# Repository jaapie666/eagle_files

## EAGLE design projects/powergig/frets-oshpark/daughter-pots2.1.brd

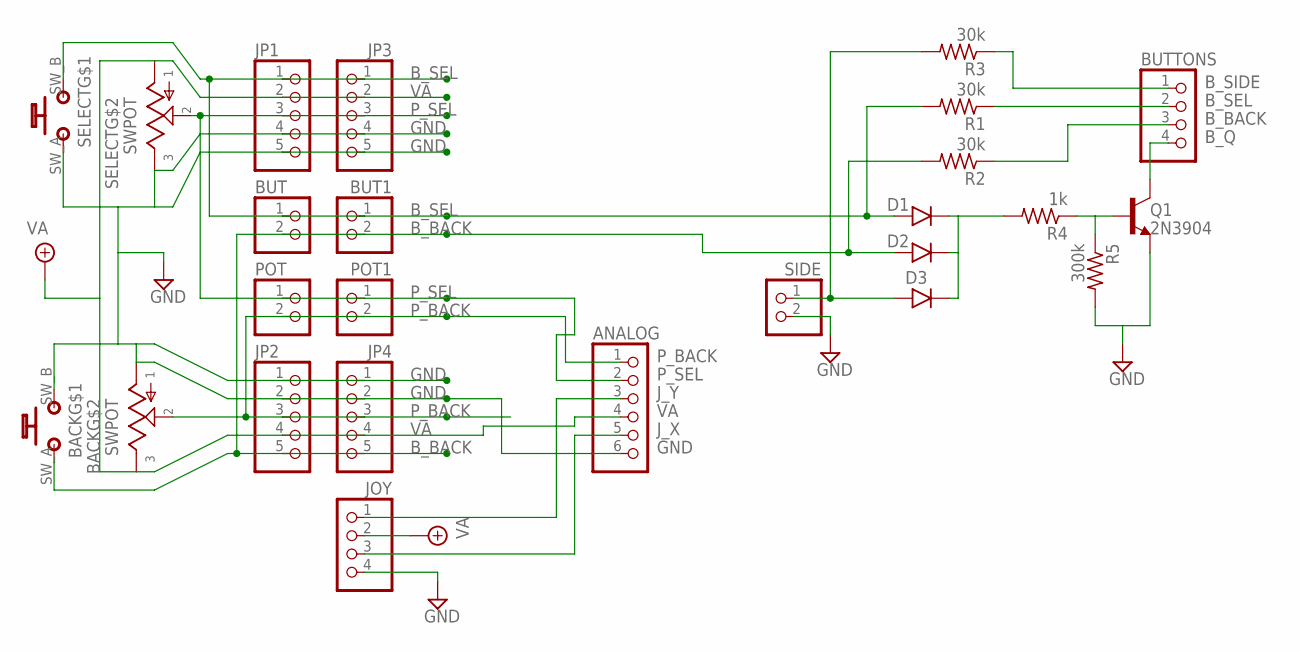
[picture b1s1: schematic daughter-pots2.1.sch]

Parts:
ANALOG: PINHD-1X6; 1X06
BACK: SWPOT
BUT, BUT1: PINHD-1X2; 1X02
BUTTONS: PINHD-1X4; 1X04
D1: 1N4148-3; DO35-3
D2: 1N4148-2; DO35-2
D3: 1N4148-4; DO35-4
JOY: PINHD-1X4; 1X04
JP1, JP2, JP3, JP4: PINHD-1X5; 1X05
POT, POT1: PINHD-1X2; 1X02
Q1: 2N3904; TO92-
R1, R2, R3: 30k; R0207/3
R4: 1k; R0207/3
R5: 300k; R0207/1V
SELECT: SWPOT
SIDE: PINHD-1X2; 1X02

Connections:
B_BACK: BACK.SW_A (B_A), BUT.2, BUT1.2, D2.A, JP2.5, JP4.5, R2.2
B_Q: BUTTONS.4, Q1.1 (C)
B_SEL: BUT.1, BUT1.1, D1.A, JP1.1, JP3.1, R1.2, SELECT.SW_B (B_B)
B_SIDE: D3.A, R3.2, SIDE.1
GND: ANALOG.6, BACK.POT_B, BACK.SW_B (B_B), JOY.4, JP1.4, JP1.5, JP2.1, JP2.2, JP3.4, JP3.5, JP4.1, JP4.2, Q1.3 (E), R5.2, SELECT.POT_A, SELECT.SW_A (B_A), SIDE.2
J_X: ANALOG.5, JOY.3
J_Y: ANALOG.3, JOY.1
unnamed: Q1.2 (B), R4.1, R5.1
unnamed: BUTTONS.2, R1.1
unnamed: BUTTONS.3, R2.1
unnamed: D1.C, D2.C, D3.C, R4.2
unnamed: BUTTONS.1, R3.1
P_BACK: ANALOG.1, BACK.POT_W, JP2.3, JP4.3, POT.2, POT1.2
P_SEL: ANALOG.2, JP1.3, JP3.3, POT.1, POT1.1, SELECT.POT_W
VA: ANALOG.4, BACK.POT_A, JOY.2, JP1.2, JP2.4, JP3.2, JP4.4, SELECT.POT_B

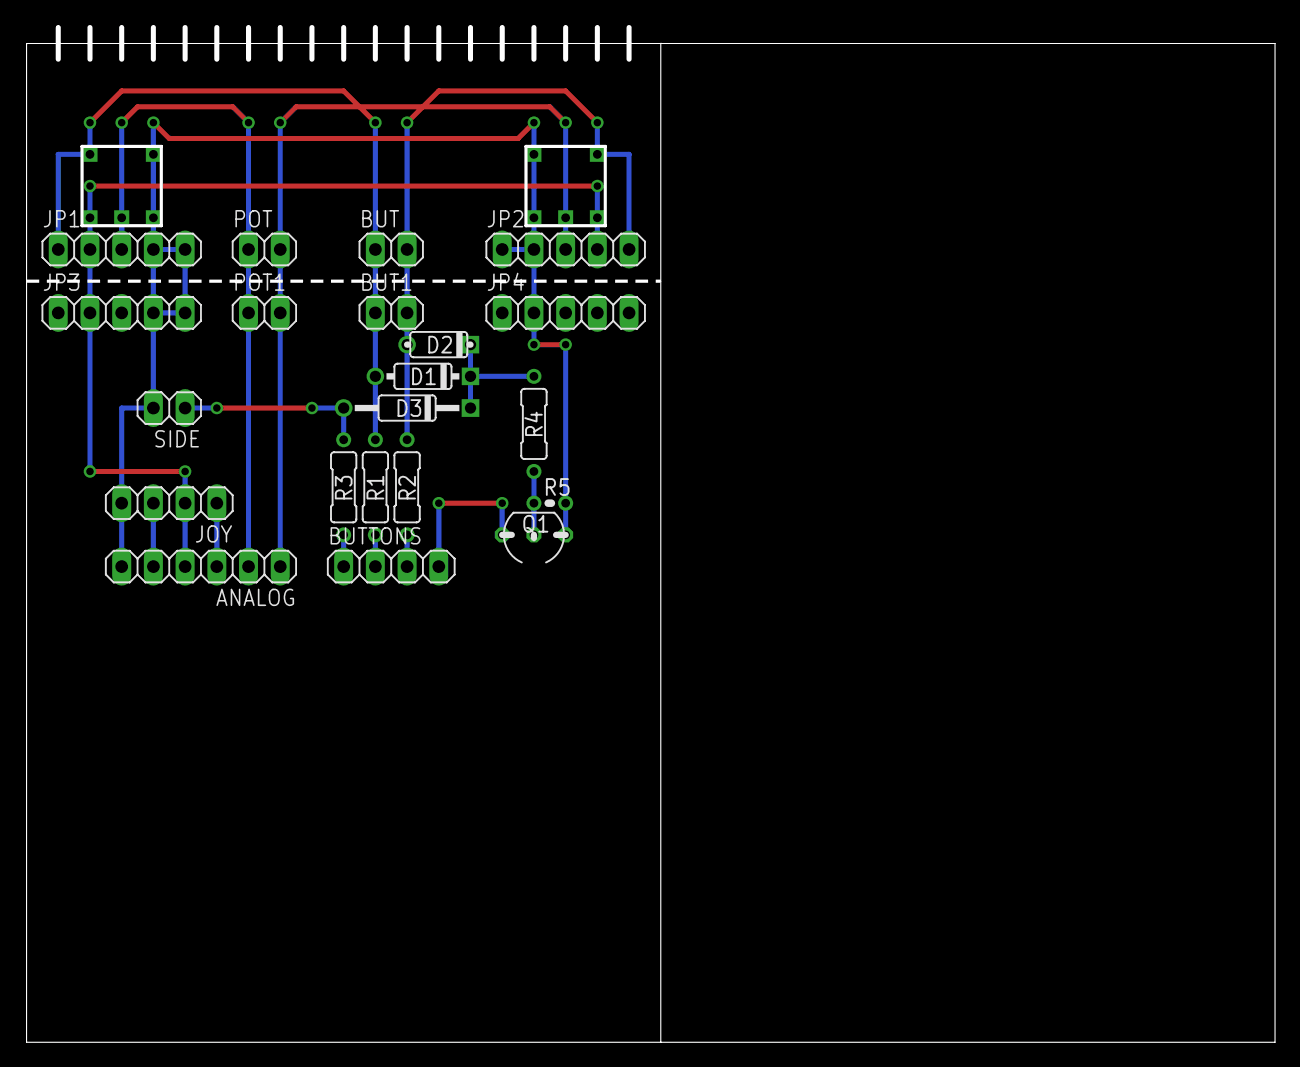
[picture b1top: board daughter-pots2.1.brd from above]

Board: 2 copper layers, 100.0 x 81.3 mm, 23 parts (0 on the bottom side), 15 nets.

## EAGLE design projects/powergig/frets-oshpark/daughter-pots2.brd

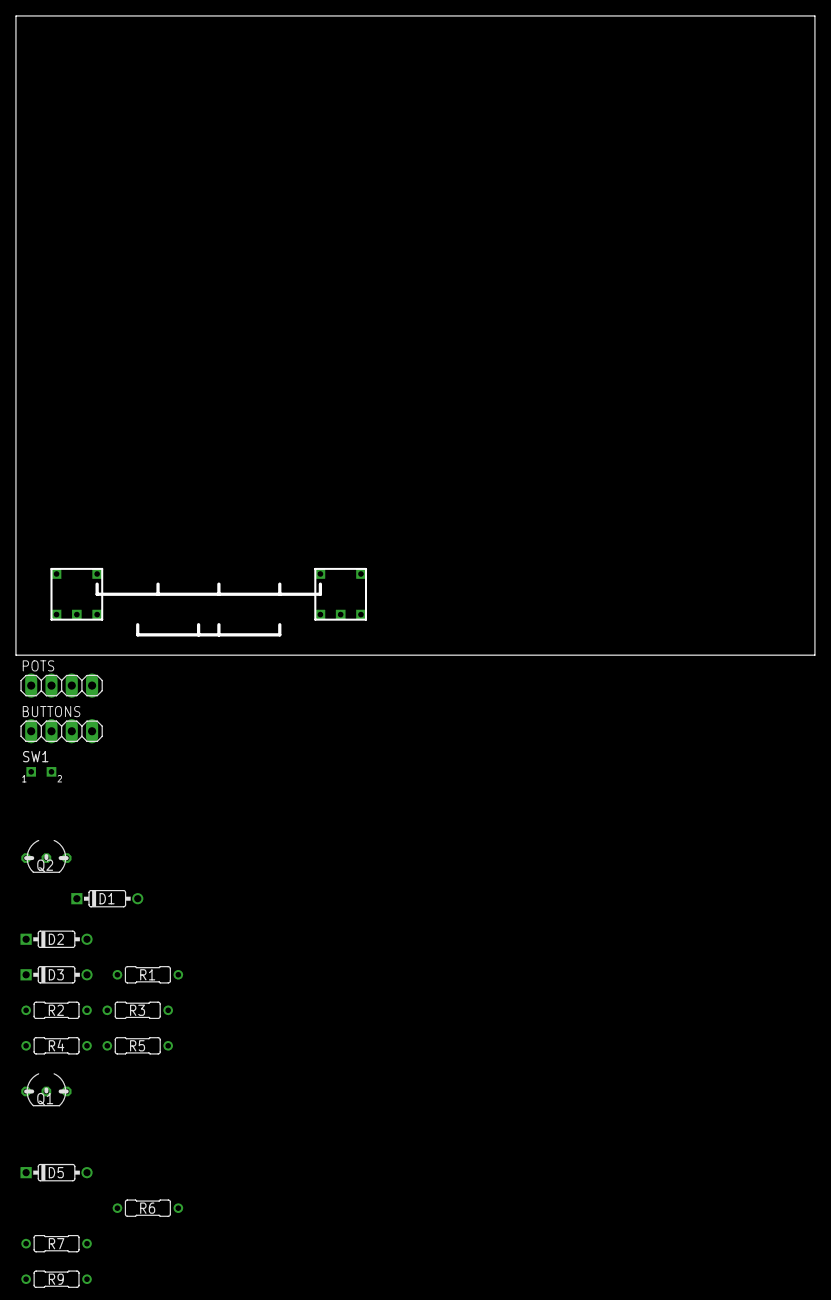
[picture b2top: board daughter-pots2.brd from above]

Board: 2 copper layers, 100.0 x 80.0 mm, 19 parts (0 on the bottom side), 15 nets, no tracks yet.

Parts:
BACK: SWPOT
BUTTONS: 1X04
D1, D2, D3, D5: 1N4148-3; DO35-3
POTS: 1X04
Q1, Q2: 2N3904; TO92-
R1, R6: 1K; R0207/3
R2, R7: 300K; R0207/3
R3, R4, R5, R9: 30k; R0207/3
SELECT: SWPOT
SW1: MOMENTARYSPST1; SPST

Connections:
BPOT: BACK.POT_W, POTS.2
B_BACK: BUTTONS.1, R3.1
B_SEL: BUTTONS.2, R4.1
B_SIDE: BUTTONS.3, R5.1
GND: BACK.POT_A, BACK.SW_B, POTS.4, Q1.3, Q2.3, R2.1, R7.1, SELECT.POT_A, SELECT.SW_B, SW1.2
unnamed: Q2.2, R1.2, R2.2
unnamed: D1.C, D2.C, D3.C, R1.1
unnamed: Q1.2, R6.2, R7.2
unnamed: D2.A, R4.2
unnamed: BACK.SW_A, D1.A, R3.2
unnamed: D3.A, R5.2, SW1.1
unnamed: D5.A, R9.2
Q: BUTTONS.4, Q2.1
SPOT: POTS.3, SELECT.POT_W
VA: BACK.POT_B, POTS.1, SELECT.POT_B

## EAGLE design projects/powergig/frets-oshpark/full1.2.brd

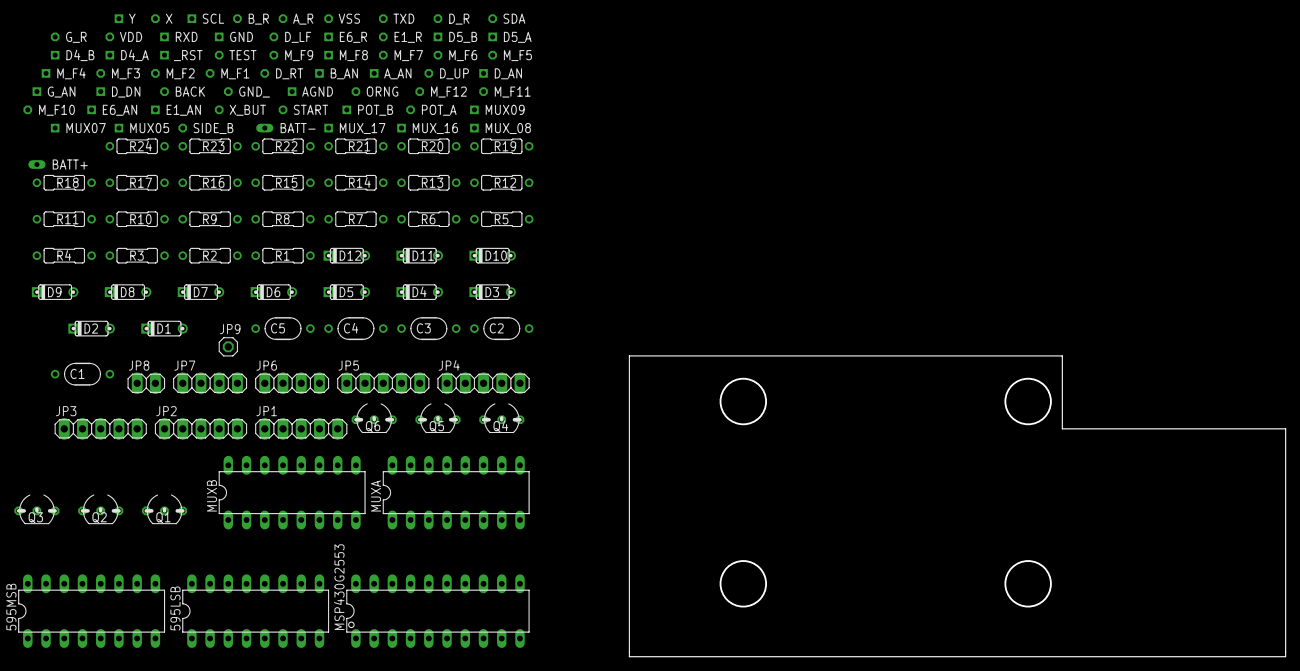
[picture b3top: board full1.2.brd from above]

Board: 2 copper layers, 91.4 x 41.9 mm, 121 parts (0 on the bottom side), 83 nets, no tracks yet.

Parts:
595LSB, 595MSB: 74LS595N; DIL16
AGND: SQUARE
A_AN: SQUARE
A_R: OCTOGON
BACK: OCTOGON
BATT+: LONG
BATT-: LONG
B_AN: SQUARE
B_R: OCTOGON
C1, C2, C3, C4, C5: 100n; 050X030_050_3
D1, D2, D3, D4, D5, D6, D7, D8, D9, D10, D11, D12: 1N4148-2; DO35-2
D4_A, D4_B, D5_A, D5_B: SQUARE
D_AN: SQUARE
D_DN: SQUARE
D_LF: OCTOGON
D_R: OCTOGON
D_RT: OCTOGON
D_UP: OCTOGON
E1_AN, E6_AN, E6_R: SQUARE
E1_R: OCTOGON
GND: SQUARE
GND_: OCTOGON
G_AN: SQUARE
G_R: OCTOGON
JP1, JP2, JP3, JP4, JP5: 1X05
JP6, JP7: 1X04
JP8: 1X02
JP9: 1X01
MSP430G2553: G2XX3---N20; N20
MUX05, MUX07, MUX09: SQUARE
MUXA: 4051N; DIL16
MUXB: 4051N; DIL16
MUX_08, MUX_16, MUX_17: SQUARE
M_F1, M_F2, M_F3, M_F5, M_F6, M_F7, M_F9, M_F10, M_F11, M_F12: OCTOGON
M_F4, M_F8: SQUARE
ORNG: OCTOGON
POT_A: OCTOGON
POT_B: SQUARE
Q1, Q2, Q3, Q4, Q5, Q6: 2N3904; TO92-
R1, R3, R5, R7, R9, R11: 300k; R0207/3
R2, R4, R6, R8, R10, R12: 1k; R0207/3
R13, R14, R15, R16, R17, R18, R19, R20, R21, R22, R23, R24: 30k; R0207/3
RXD: SQUARE
SCL: SQUARE
SDA: OCTOGON
SIDE_B: OCTOGON
START: OCTOGON
TEST: OCTOGON
TXD: OCTOGON
VDD: OCTOGON
VSS: OCTOGON
X: OCTOGON
X_BUT: OCTOGON
Y: SQUARE
_RST: SQUARE

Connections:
A_AN: A_AN.1, MUXB.2
A_IN: MSP430G2553.2, MUXA.3, MUXB.3
BACK: BACK.1, R18.1
B_AN: B_AN.1, MUXB.12
D0: E6_R.1, MSP430G2553.5, Q3.1
D1: A_R.1, MSP430G2553.6, Q2.1
D2: D_R.1, MSP430G2553.7, Q1.1
D3: G_R.1, MSP430G2553.8, Q6.1
D4: B_R.1, MSP430G2553.9, Q5.1
D5: E1_R.1, MSP430G2553.10, Q4.1
D_AN: D_AN.1, MUXB.5
D_DOWN: D_DN.1, R22.1
D_RIGHT: D_RT.1, R21.1
D_UP: D_UP.1, R19.1
E1_AN: E1_AN.1, MUXB.15
E6_AN: E6_AN.1, MUXB.4
GND: 595LSB.8, 595LSB.13, 595MSB.8, 595MSB.13, BATT-.1, C1.2, C2.2, C3.2, C4.2, C5.2, GND.1, GND_.1, MSP430G2553.20, MUXA.7, MUXA.8, MUXB.7, MUXB.8, Q1.3, Q2.3, Q3.3, Q4.3, Q5.3, Q6.3, R1.2, R3.2, R5.2, R7.2, R9.2, R11.2, VSS.1
G_AN: G_AN.1, MUXB.1
INH_A: MSP430G2553.18, MUXA.6
INH_B: MSP430G2553.19, MUXB.6
JOY_X: MUXA.4, X.1
JOY_Y: MUXA.2, Y.1
MUX05: MUX05.1, MUXA.12
MUX07: MUX07.1, MUXA.15
MUX08: MUXA.14, MUX_08.1
MUX09: MUX09.1, MUXA.13
MUX16: MUXB.14, MUX_16.1
MUX17: MUXB.13, MUX_17.1
unnamed: 595LSB.14, 595MSB.9
unnamed: Q2.2, R3.1, R4.2
unnamed: D3.A, R15.2
unnamed: D5.C, D9.C, R4.1
unnamed: Q3.2, R5.1, R6.2
unnamed: Q1.2, R1.1, R2.2
unnamed: D6.C, D8.C, R2.1
unnamed: D4.A, R16.2
unnamed: D5.A, R17.2
unnamed: D4.C, D7.C, R6.1
unnamed: Q4.2, R7.1, R8.2
unnamed: D6.A, R18.2
unnamed: D3.C, D12.C, R8.1
unnamed: Q5.2, R9.1, R10.2
unnamed: D1.A, R13.2
unnamed: D2.C, D11.C, R10.1
unnamed: Q6.2, R11.1, R12.2
unnamed: D2.A, R14.2
unnamed: D1.C, D10.C, R12.1
unnamed: D7.A, R19.2
unnamed: D8.A, R20.2
unnamed: D9.A, R21.2
unnamed: D10.A, R22.2
unnamed: D4_B.1, R14.1
unnamed: D5_B.1, R15.1
unnamed: D11.A, R23.2
unnamed: D12.A, R24.2
unnamed: D4_A.1, R23.1
unnamed: D5_A.1, R24.1
POT_B: MUXA.1, POT_B.1
RCK: 595LSB.12, 595MSB.12, MSP430G2553.13
RXD: MSP430G2553.3, RXD.1
SCK: 595LSB.11, 595MSB.11, MSP430G2553.12
SCL: MSP430G2553.14, SCL.1
SDA: MSP430G2553.15, SDA.1
SER: 595MSB.14, MSP430G2553.11
SR0: 595LSB.7, MUXA.11, MUXB.11
SR1: 595LSB.6, MUXA.10, MUXB.10
SR2: 595LSB.5, MUXA.9, MUXB.9
SR4: 595LSB.3, M_F12.1
SR5: 595LSB.2, M_F11.1
SR6: 595LSB.1, M_F10.1
SR7: 595LSB.15, M_F9.1
SR8: 595MSB.7, M_F8.1
SR10: 595MSB.5, M_F6.1
SR11: 595MSB.4, M_F5.1
SR12: 595MSB.3, M_F4.1
SR14: 595MSB.1, M_F2.1
SR15: 595MSB.15, M_F1.1
START: R13.1, START.1
TEST: MSP430G2553.17, TEST.1
TXD: MSP430G2553.4, TXD.1
VA: 595LSB.10, 595LSB.16, 595MSB.10, 595MSB.16, BATT+.1, C1.1, C2.1, C3.1, C4.1, C5.1, MSP430G2553.1, MUXA.16, MUXB.16, VDD.1
X_BUTTON: R16.1, X_BUT.1
_RST: MSP430G2553.16, _RST.1

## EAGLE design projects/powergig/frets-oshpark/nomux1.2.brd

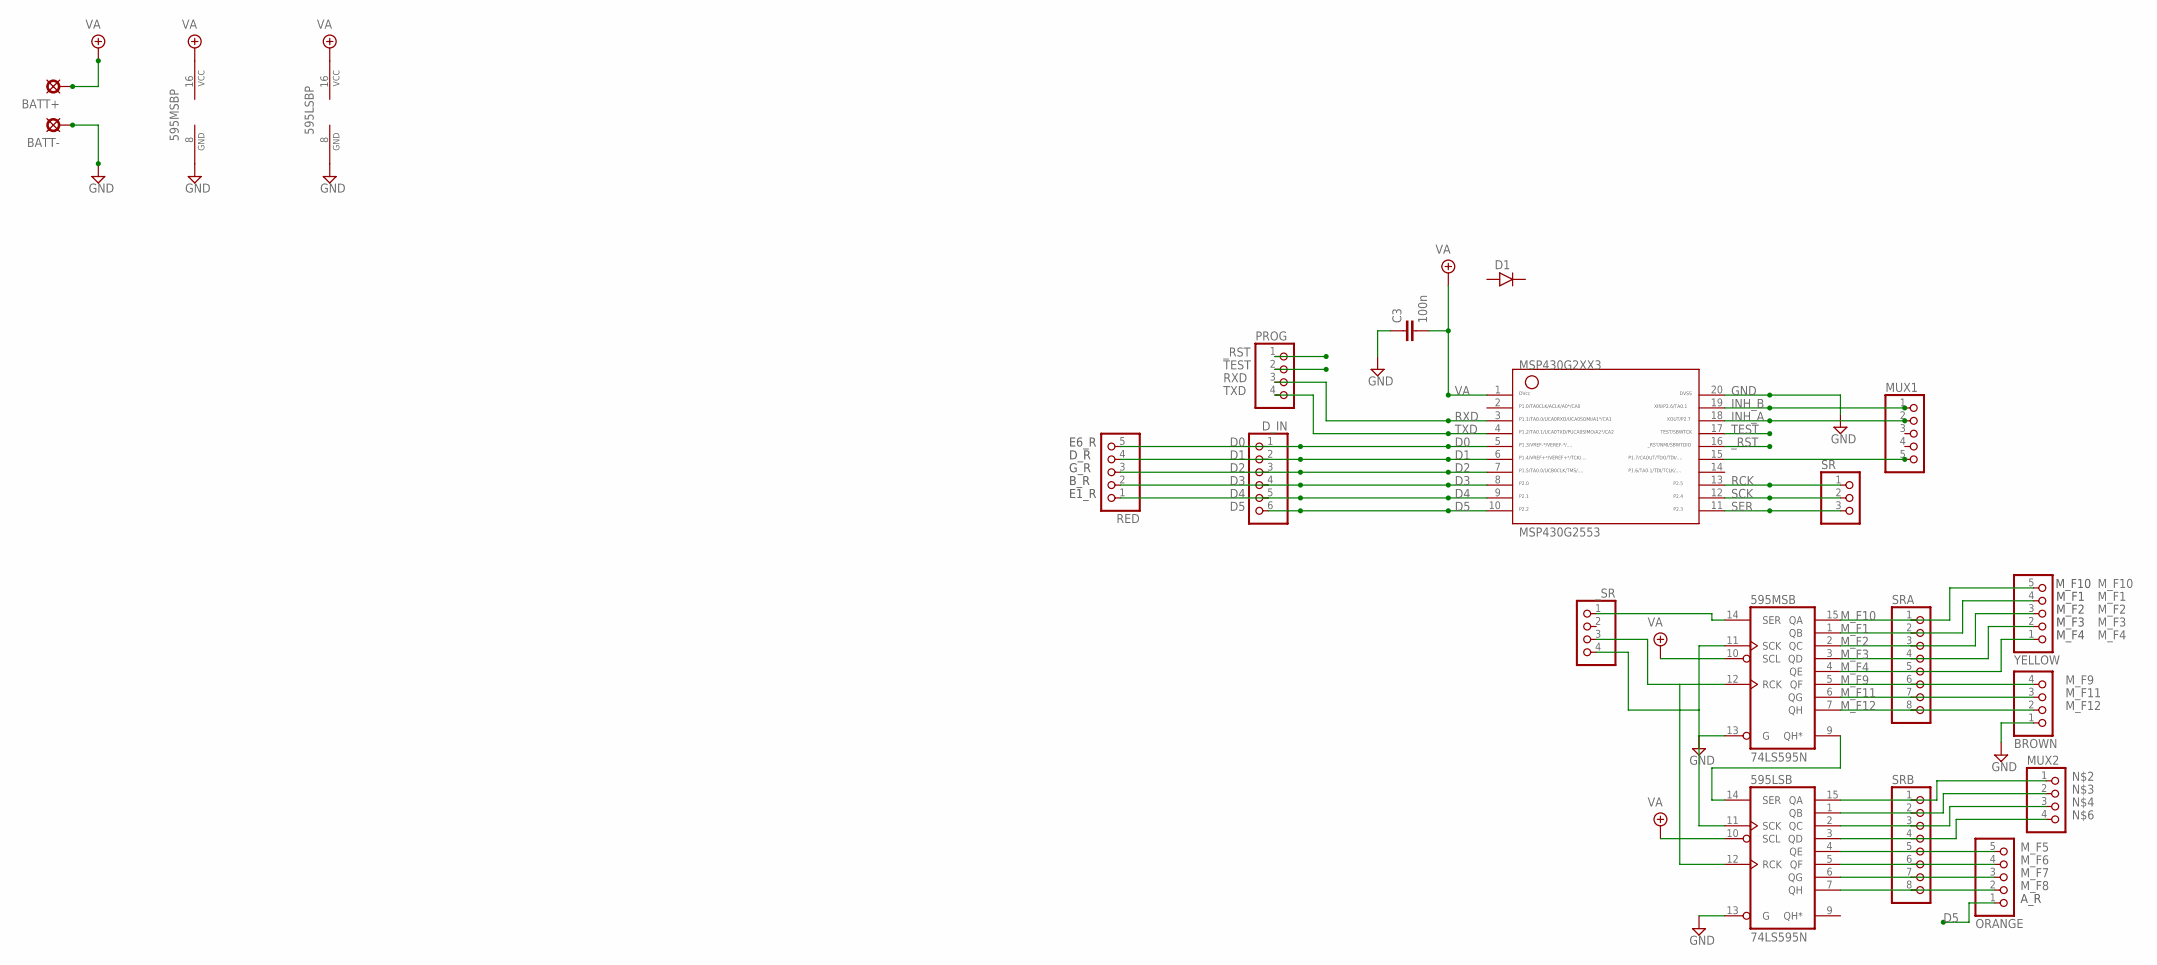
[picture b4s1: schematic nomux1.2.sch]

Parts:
595LSB, 595MSB: 74LS595N; DIL16
BATT+: PADL; LONG
BATT-: PADL; LONG
BROWN: PINHD-1X4; 1X04
C3: 100n; 050X030_050_3
D1: 1N400X.4; DO41-4
D_IN: PINHD-1X6; 1X06
MSP430G2553: G2XX3---N20; N20
MUX1: PINHD-1X5; 1X05
MUX2: PINHD-1X4; 1X04
ORANGE: PINHD-1X5; 1X05
PROG: PINHD-1X4; 1X04
RED: PINHD-1X5; 1X05
SR: PINHD-1X3; 1X03
SRA: PINHD-1X8; 1X08
SRB: PINHD-1X8; 1X08
YELLOW: PINHD-1X5; 1X05
_SR: PINHD-1X4; 1X04

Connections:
D0: D_IN.1, MSP430G2553.5, RED.5
D1: D_IN.2, MSP430G2553.6, RED.4
D2: D_IN.3, MSP430G2553.7, RED.3
D3: D_IN.4, MSP430G2553.8, RED.2
D4: D_IN.5, MSP430G2553.9, RED.1
D5: D_IN.6, MSP430G2553.10, ORANGE.1
GND: 595LSB.8 (GND), 595LSB.13 (G), 595MSB.8 (GND), 595MSB.13 (G), BATT-.1, BROWN.1, C3.1, MSP430G2553.20
INH_A: MSP430G2553.18, MUX1.2
INH_B: MSP430G2553.19, MUX1.1
M_F1: 595MSB.1 (QB), SRA.2, YELLOW.4
M_F2: 595MSB.2 (QC), SRA.3, YELLOW.3
M_F3: 595MSB.3 (QD), SRA.4, YELLOW.2
M_F4: 595MSB.4 (QE), SRA.5, YELLOW.1
M_F5: 595LSB.4 (QE), ORANGE.5, SRB.5
M_F6: 595LSB.5 (QF), ORANGE.4, SRB.6
M_F7: 595LSB.6 (QG), ORANGE.3, SRB.7
M_F8: 595LSB.7 (QH), ORANGE.2, SRB.8
M_F9: 595MSB.5 (QF), BROWN.4, SRA.6
M_F10: 595MSB.15 (QA), SRA.1, YELLOW.5
M_F11: 595MSB.6 (QG), BROWN.3, SRA.7
M_F12: 595MSB.7 (QH), BROWN.2, SRA.8
unnamed: 595LSB.14 (SER), 595MSB.9 (QH*)
unnamed: 595LSB.15 (QA), MUX2.1, SRB.1
unnamed: 595LSB.1 (QB), MUX2.2, SRB.2
unnamed: 595LSB.2 (QC), MUX2.3, SRB.3
unnamed: 595LSB.3 (QD), MUX2.4, SRB.4
unnamed: MSP430G2553.15, MUX1.5
unnamed: 595MSB.14 (SER), _SR.1
unnamed: 595LSB.11 (SCK), 595MSB.11 (SCK), _SR.4
unnamed: 595LSB.12 (RCK), 595MSB.12 (RCK), _SR.3
RCK: MSP430G2553.13, SR.1
RXD: MSP430G2553.3, PROG.3
SCK: MSP430G2553.12, SR.2
SER: MSP430G2553.11, SR.3
TEST: MSP430G2553.17, PROG.2
TXD: MSP430G2553.4, PROG.4
VA: 595LSB.10 (SCL), 595LSB.16 (VCC), 595MSB.10 (SCL), 595MSB.16 (VCC), BATT+.1, C3.2, MSP430G2553.1
_RST: MSP430G2553.16, PROG.1

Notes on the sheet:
M_F10
M_F1
M_F2
M_F3
M_F4
E6_R
D_R
G_R
B_R
E1_R
A_R

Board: 2 copper layers, 19 parts (0 on the bottom side), 38 nets, no tracks yet.

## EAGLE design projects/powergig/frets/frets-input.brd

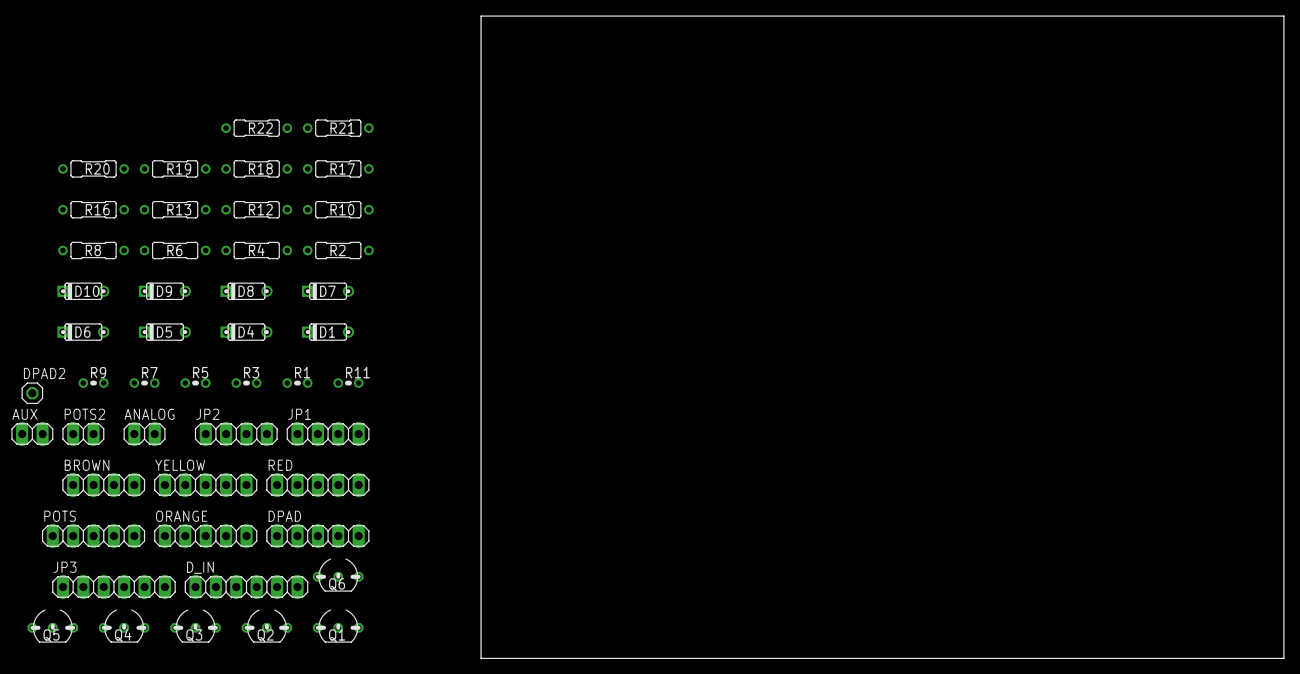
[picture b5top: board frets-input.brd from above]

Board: 2 copper layers, 100.0 x 80.0 mm, 48 parts (0 on the bottom side), 49 nets, no tracks yet.

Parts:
ANALOG: 1X02
AUX: 1X02
BROWN: 1X04
D1, D4, D5, D6, D7, D8, D9, D10: 1N4148-2; DO35-2
DPAD: 1X05
DPAD2: 1X01
D_IN: 1X06
JP1, JP2: 1X04
JP3: 1X06
ORANGE: 1X05
POTS: 1X05
POTS2: 1X02
Q1, Q2, Q3, Q4, Q5, Q6: 2N3904; TO92-
R1, R3, R5, R7, R9, R11: 300k; R0207/1V
R2, R4, R6, R8, R10, R12: 1k; R0207/3
R13, R16, R17, R18, R19, R20, R21, R22: 30k; R0207/3
RED: 1X05
YELLOW: 1X05

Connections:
D0: D_IN.1, Q3.1, RED.5
D1: D_IN.2, ORANGE.5, Q2.1
D2: D_IN.3, Q1.1, RED.4
D3: D_IN.4, Q6.1, RED.3
D4: D_IN.5, Q5.1, RED.2
D5: D_IN.6, Q4.1, RED.1
D_DOWN: DPAD.1, R22.1
D_LEFT: DPAD.2, R20.1
D_RIGHT: DPAD.3, R21.1
D_UP: DPAD.4, R19.1
GND: BROWN.1, DPAD2.1, JP3.6, POTS2.1, Q1.3, Q2.3, Q3.3, Q4.3, Q5.3, Q6.3, R1.2, R3.2, R5.2, R7.2, R9.2, R11.2
M_F1: JP1.1, YELLOW.4
M_F2: JP1.2, YELLOW.3
M_F3: JP1.3, YELLOW.2
M_F4: JP1.4, YELLOW.1
M_F5: JP2.1, ORANGE.4
M_F6: JP2.2, ORANGE.3
M_F7: JP2.3, ORANGE.2
M_F8: JP2.4, ORANGE.1
M_F9: BROWN.4, JP3.1
M_F10: JP3.2, YELLOW.5
M_F11: BROWN.3, JP3.3
M_F12: BROWN.2, JP3.4
unnamed: Q2.2, R3.1, R4.2
unnamed: AUX.2, R10.1
unnamed: D5.C, D9.C, R4.1
unnamed: Q3.2, R5.1, R6.2
unnamed: Q1.2, R1.1, R2.2
unnamed: D6.C, D8.C, R2.1
unnamed: D4.A, R16.2
unnamed: D5.A, R17.2
unnamed: D4.C, D7.C, R6.1
unnamed: Q4.2, R7.1, R8.2
unnamed: D6.A, R18.2
unnamed: AUX.1, R8.1
unnamed: Q5.2, R9.1, R10.2
unnamed: D1.A, R13.2
unnamed: Q6.2, R11.1, R12.2
unnamed: D1.C, D10.C, R12.1
unnamed: D7.A, R19.2
unnamed: D8.A, R20.2
unnamed: D9.A, R21.2
unnamed: D10.A, R22.2
ORNG: JP3.5, POTS2.2
POT_A: ANALOG.2, POTS.2
POT_B: ANALOG.1, POTS.1
SIDE_B: POTS.5, R17.1
START: POTS.3, R13.1
X_BUTTON: DPAD.5, R16.1

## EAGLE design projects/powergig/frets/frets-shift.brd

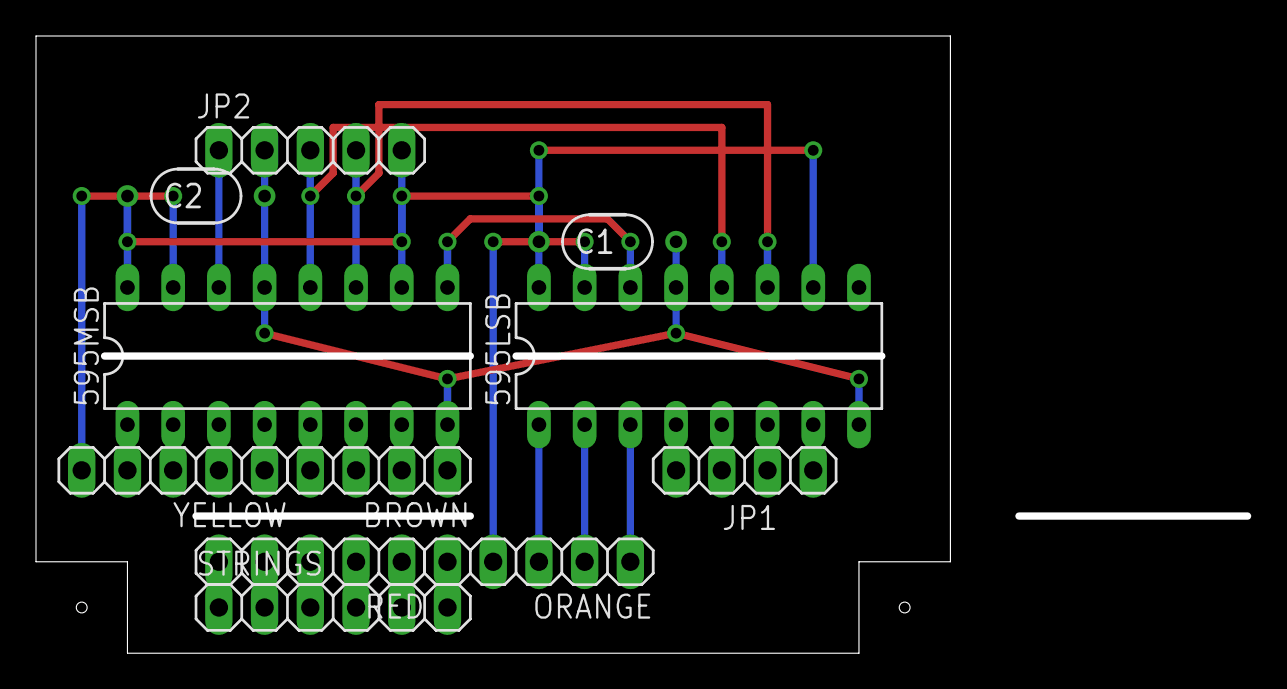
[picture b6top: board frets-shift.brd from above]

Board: 2 copper layers, 50.8 x 34.3 mm, 11 parts (0 on the bottom side), 28 nets.

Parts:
595LSB, 595MSB: 74LS595N; DIL16
BROWN: 1X04
C1, C2: 100n; 050X030_050_3
JP1: 1X04
JP2: 1X05
ORANGE: 1X05
RED: 1X05
STRINGS: 1X06
YELLOW: 1X05

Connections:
D0: RED.5, STRINGS.1
D1: RED.4, STRINGS.2
D2: RED.3, STRINGS.3
D3: RED.2, STRINGS.4
D4: RED.1, STRINGS.5
D5: ORANGE.5, STRINGS.6
GND: 595LSB.8, 595LSB.13, 595MSB.8, 595MSB.13, BROWN.1, C1.2, C2.2, JP2.2
MX_A: 595LSB.5, JP1.2
MX_B: 595LSB.6, JP1.3
MX_C: 595LSB.7, JP1.4
unnamed: 595LSB.14, 595MSB.9
ORNG: 595LSB.4, JP1.1
RCK: 595LSB.12, 595MSB.12, JP2.3
SCK: 595LSB.11, 595MSB.11, JP2.4
SER: 595MSB.14, JP2.1
SR4: 595LSB.3, ORANGE.1
SR5: 595LSB.2, ORANGE.2
SR6: 595LSB.1, ORANGE.3
SR7: 595LSB.15, ORANGE.4
SR8: 595MSB.7, BROWN.2
SR9: 595MSB.6, BROWN.3
SR10: 595MSB.5, BROWN.4
SR11: 595MSB.4, YELLOW.1
SR12: 595MSB.3, YELLOW.2
SR13: 595MSB.2, YELLOW.3
SR14: 595MSB.1, YELLOW.4
SR15: 595MSB.15, YELLOW.5
VA: 595LSB.10, 595LSB.16, 595MSB.10, 595MSB.16, C1.1, C2.1, JP2.5

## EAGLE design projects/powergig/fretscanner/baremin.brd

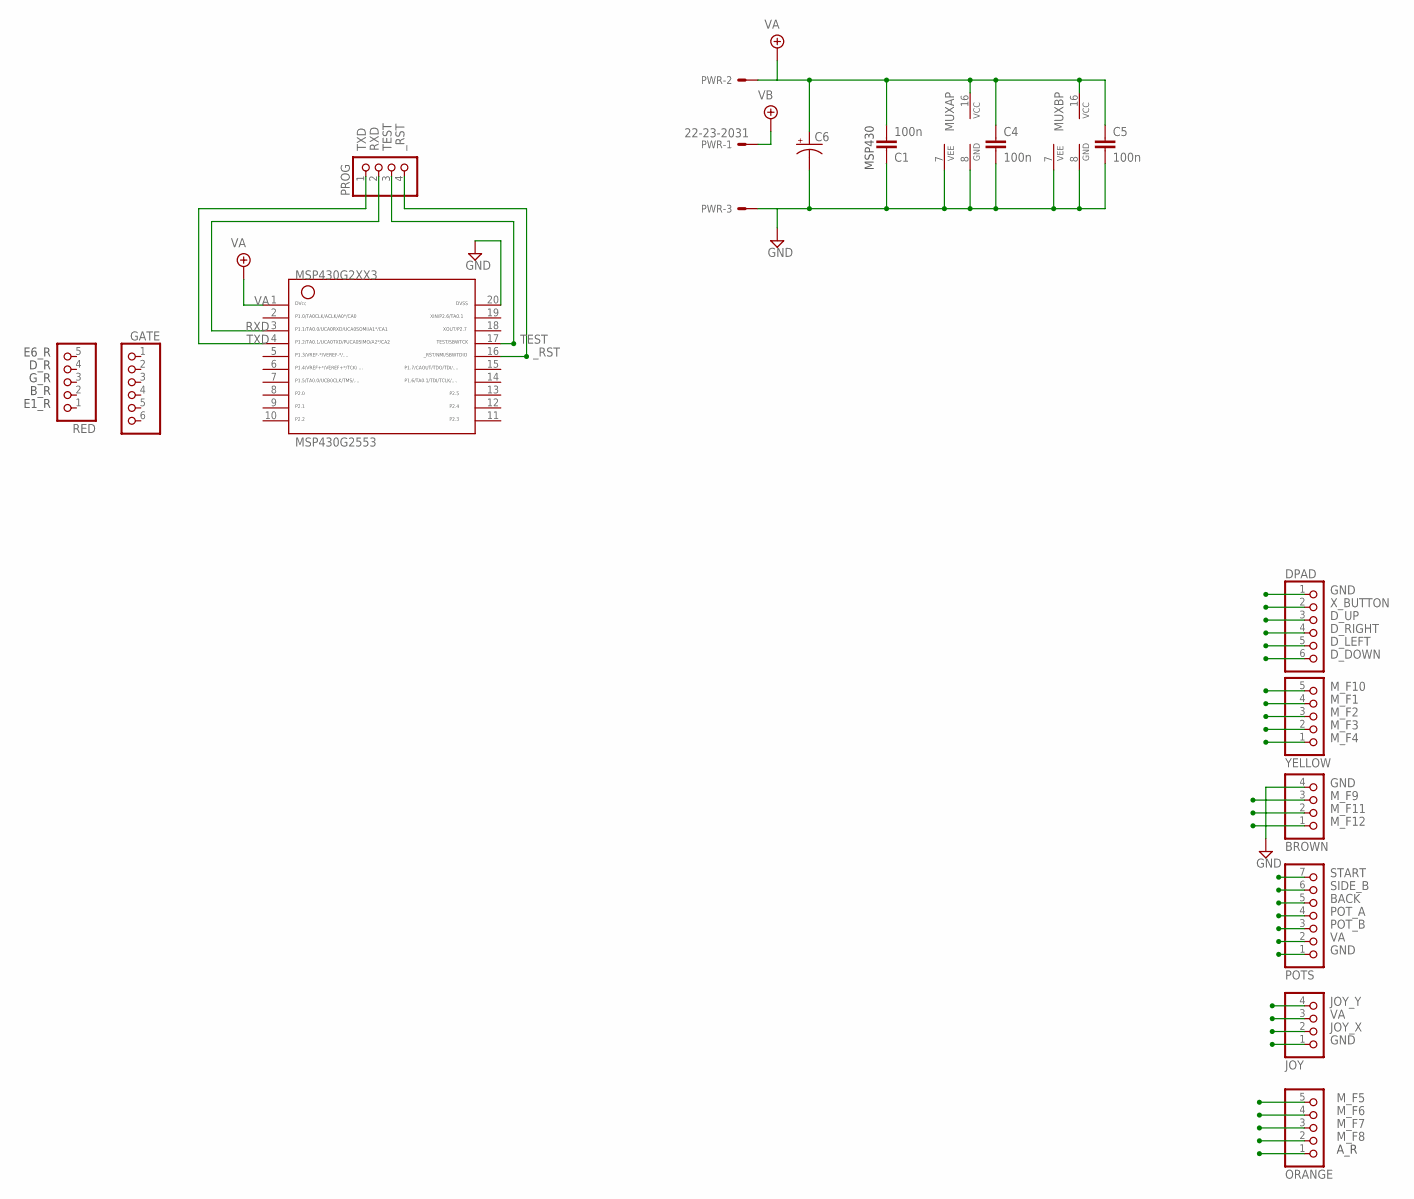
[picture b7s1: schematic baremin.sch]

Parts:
BROWN: PINHD-1X4; 1X04
C1, C5: 100n; 050X030_050_3
C4: 100n; 050X030_050_1
C6: 0501; 050_020_1
DPAD: PINHD-1X6; 1X06
GATE: PINHD-1X6; 1X06
JOY: PINHD-1X4; 1X04
MSP430G2553: G2XX3---N20; N20
MUXA: 4051N; DIL16
MUXB: 4052N; DIL16
ORANGE: PINHD-1X5; 1X05
POTS: PINHD-1X7; 1X07
PROG: PINHD-1X4; 1X04
PWR: 22-23-2031
RED: PINHD-1X5; 1X05
YELLOW: PINHD-1X5; 1X05

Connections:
BACK: POTS.7
D5: ORANGE.1
D_DOWN: DPAD.6
D_LEFT: DPAD.5
D_RIGHT: DPAD.4
D_UP: DPAD.3
GND: BROWN.4, C1.1, C4.2, C5.2, C6.-, DPAD.1, JOY.1, MSP430G2553.20, MUXA.7 (VEE), MUXA.8 (GND), MUXB.7 (VEE), MUXB.8 (GND), POTS.1, PWR.3
JOY_X: JOY.2
JOY_Y: JOY.4
M_F1: YELLOW.4
M_F2: YELLOW.3
M_F3: YELLOW.2
M_F4: YELLOW.1
M_F5: ORANGE.5
M_F6: ORANGE.4
M_F7: ORANGE.3
M_F8: ORANGE.2
M_F9: BROWN.3
M_F10: YELLOW.5
M_F11: BROWN.2
M_F12: BROWN.1
POT_A: POTS.4
POT_B: POTS.3
RXD: MSP430G2553.3, PROG.2
SIDE_B: POTS.6
START: POTS.5
TEST: MSP430G2553.17, PROG.3
TXD: MSP430G2553.4, PROG.1
VA: C1.2, C4.1, C5.1, C6.+, JOY.3, MSP430G2553.1, MUXA.16 (VCC), MUXB.16 (VCC), POTS.2, PWR.2
VB: PWR.1
X_BUTTON: DPAD.2
_RST: MSP430G2553.16, PROG.4

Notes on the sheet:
E6_R
D_R
G_R
B_R
E1_R
A_R
MSP430

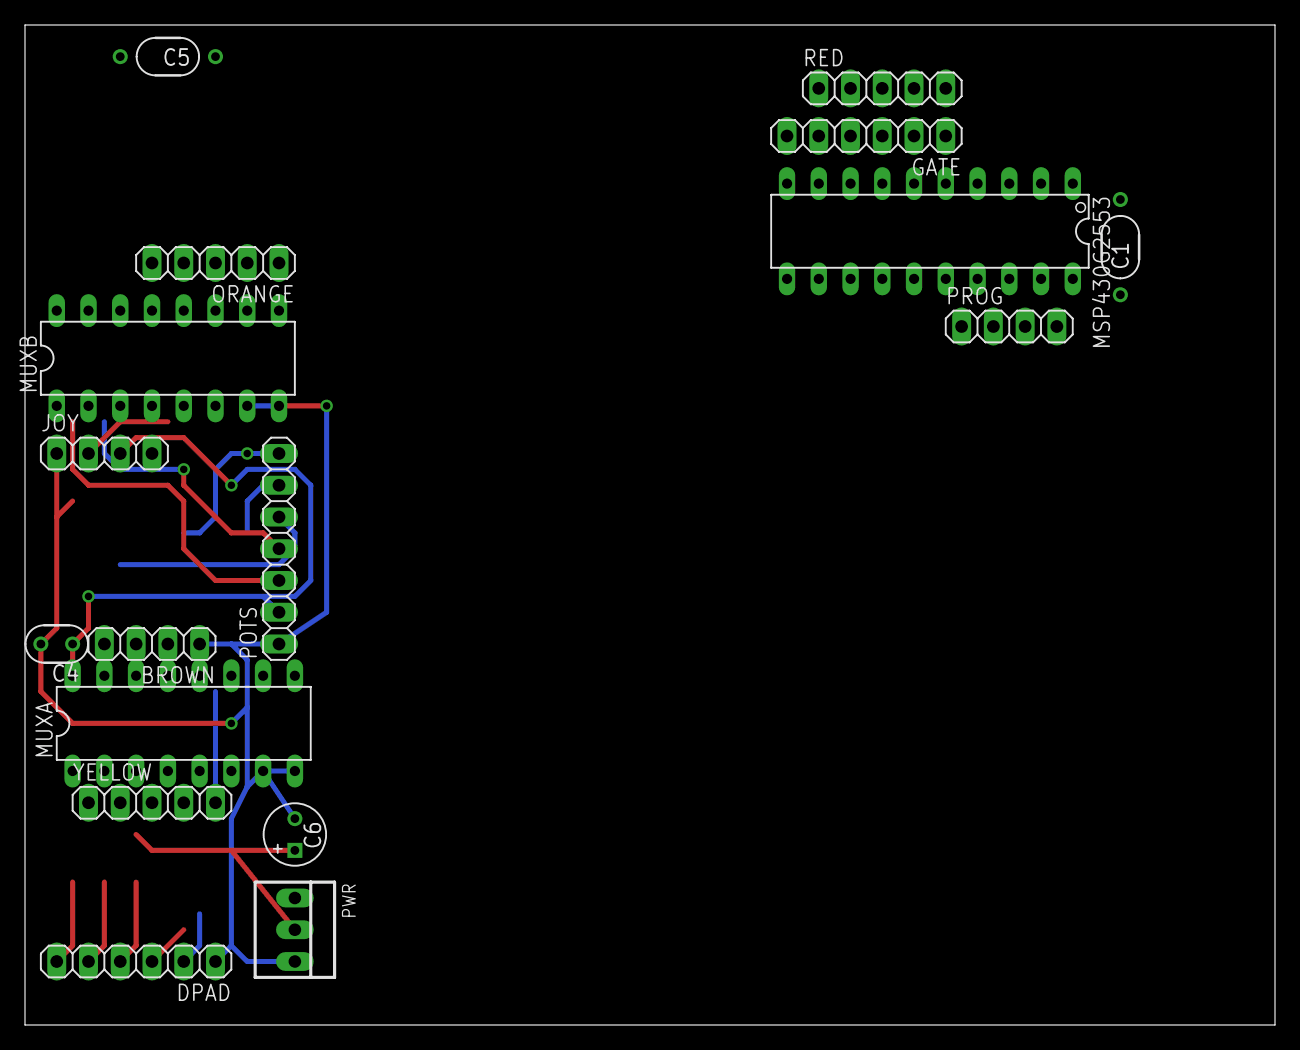
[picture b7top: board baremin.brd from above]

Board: 2 copper layers, 100.0 x 80.0 mm, 17 parts (0 on the bottom side), 6 nets.
